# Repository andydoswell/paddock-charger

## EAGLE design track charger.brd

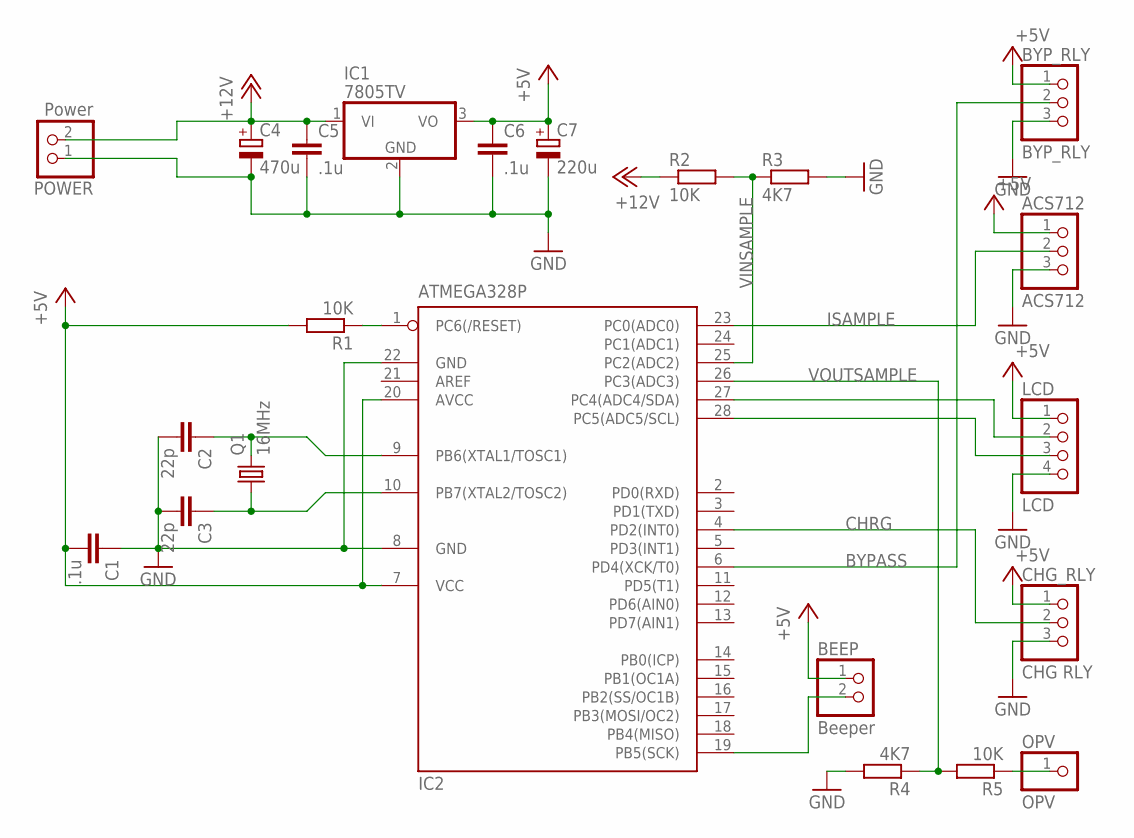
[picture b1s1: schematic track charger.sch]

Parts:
ACS712: ACS712; 1X03
BEEP: Beeper; 1X02
BYP_RLY: BYP_RLY; 1X03
C1, C5, C6: .1u; C025-024X044
C2, C3: 22p; C025-024X044
C4: 470u; E3,5-10
C7: 220u; E2,5-7
CHG_RLY: CHG RLY; 1X03
IC1: 7805TV; TO220V
IC2: ATMEGA328P; DIL28-3
LCD: LCD; 1X04
OPV: OPV; 1X01
POWER: Power; 1X02
Q1: 16MHz; HC18U-V
R1, R2, R5: 10K; 0204/7
R3, R4: 4K7; 0204/7

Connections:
+5V: ACS712.1, BEEP.1, BYP_RLY.1, C1.2, C6.1, C7.+, CHG_RLY.1, IC1.3 (VO), IC2.7 (VCC), IC2.20 (AVCC), LCD.1, R1.2
+12V: C4.+, C5.1, IC1.1 (VI), POWER.2, R2.1
BYPASS: BYP_RLY.2, IC2.6 (PD4(XCK/T0))
CHRG: CHG_RLY.2, IC2.4 (PD2(INT0))
GND: ACS712.3, BYP_RLY.3, C1.1, C2.2, C3.2, C4.-, C5.2, C6.2, C7.-, CHG_RLY.3, IC1.2 (GND), IC2.8 (GND), IC2.22 (GND), LCD.4, POWER.1, R3.2, R4.2
ISAMPLE: ACS712.2, IC2.23 (PC0(ADC0))
unnamed: IC2.27 (PC4(ADC4/SDA)), LCD.2
unnamed: IC2.28 (PC5(ADC5/SCL)), LCD.3
unnamed: OPV.1, R5.1
unnamed: C3.1, IC2.10 (PB7(XTAL2/TOSC2)), Q1.1
unnamed: BEEP.2, IC2.19 (PB5(SCK))
unnamed: C2.1, IC2.9 (PB6(XTAL1/TOSC1)), Q1.2
unnamed: IC2.1 (PC6(/RESET)), R1.1
VINSAMPLE: IC2.25 (PC2(ADC2)), R2.2, R3.1
VOUTSAMPLE: IC2.26 (PC3(ADC3)), R4.1, R5.2

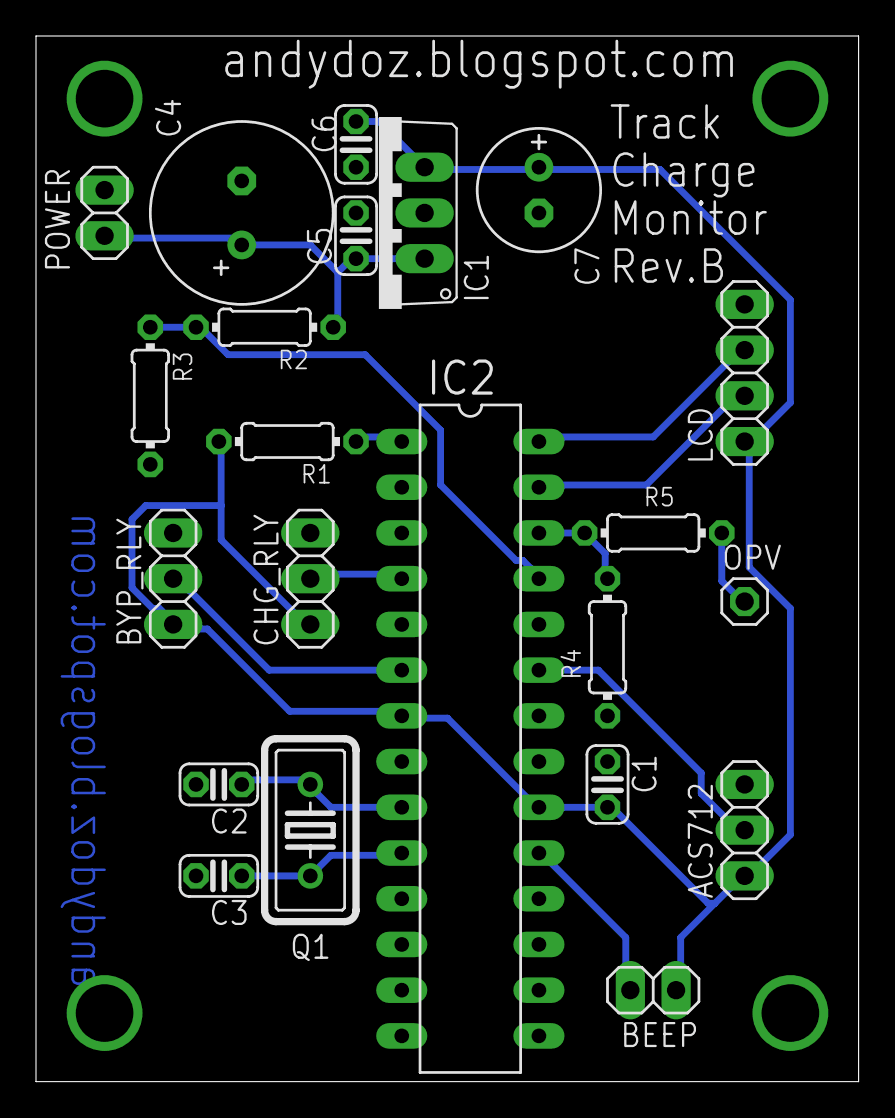
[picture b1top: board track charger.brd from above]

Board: 2 copper layers, 45.7 x 58.1 mm, 22 parts (0 on the bottom side), 15 nets.
